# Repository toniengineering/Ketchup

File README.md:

So this is KETCHUP based on a ketchup bottle but with a little twist. So I like ketchup and with the pcb board I was inspired to use it in the project. With this I made the pcb base look like a ketchup bottle. The LEDs on it form a cap at the top then will blink in a little wave loop under it. It starts at ketchup, then loop, then the word finish where the last LED is.

BOM:

|Name   |Purpose|Quantity|Total Cost (USD)|Link                                  |Distributor|
|-------|-------|--------|----------------|--------------------------------------|-----------|
|Ketchup|my pcb |5       |2.00            |https://cart.jlcpcb.com/shopcart/cart/|JLCPCB     |

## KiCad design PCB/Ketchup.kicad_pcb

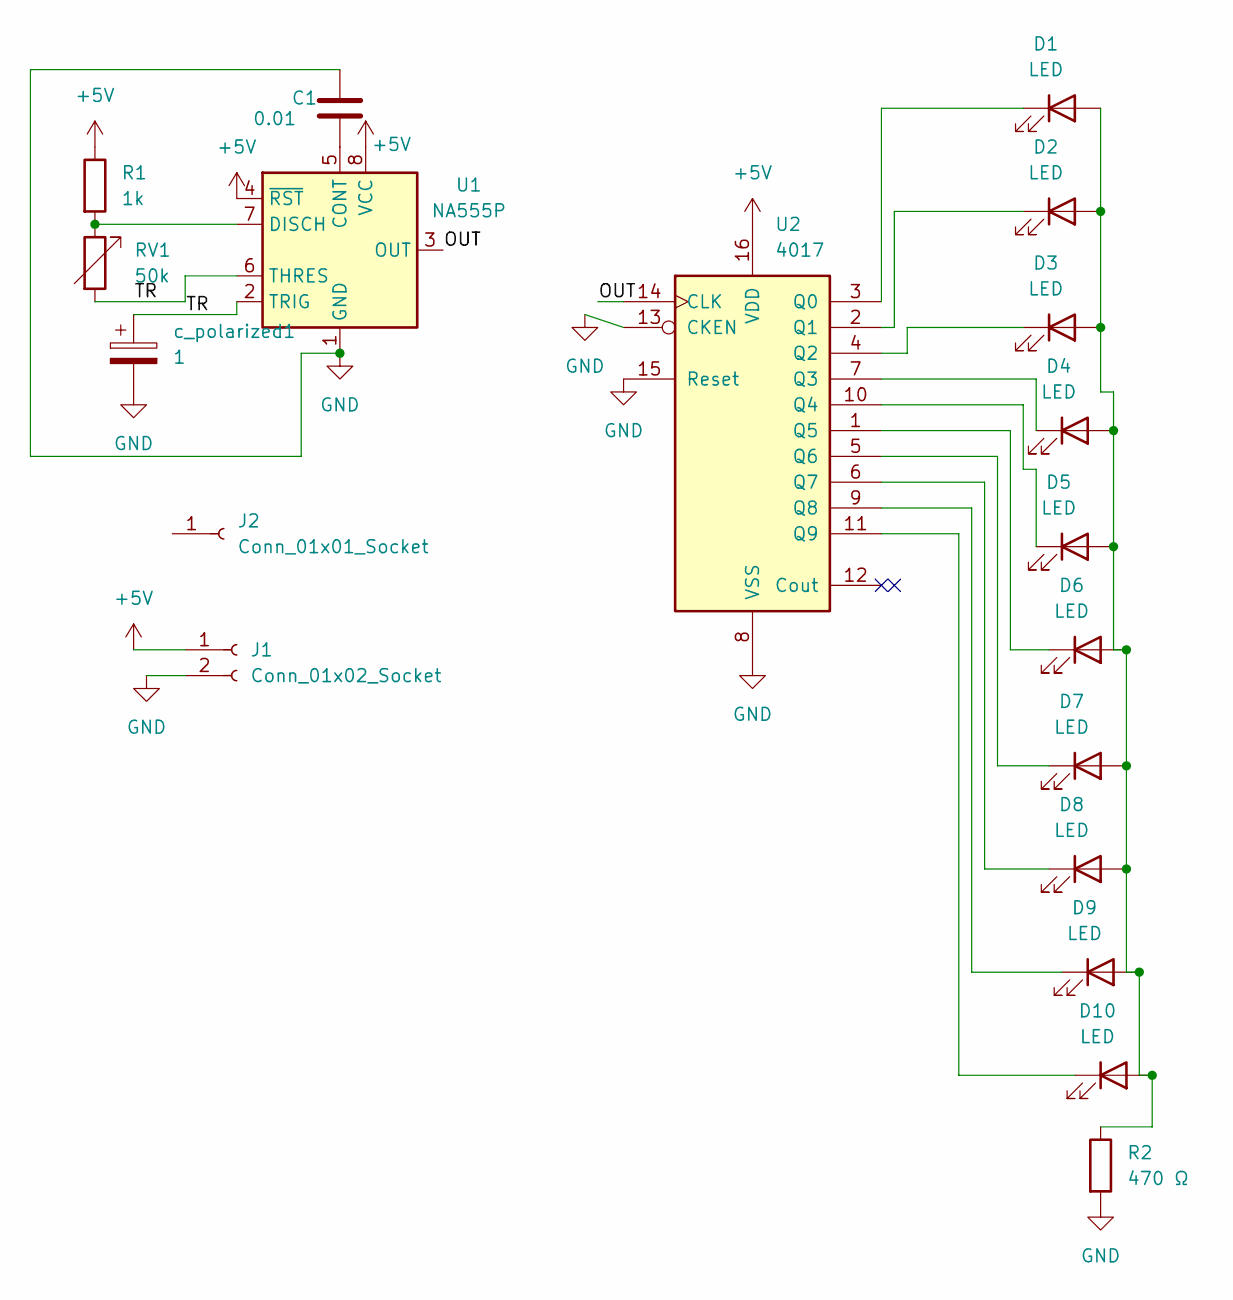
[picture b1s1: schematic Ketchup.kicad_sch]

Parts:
C1: 0.01; CP_Radial_D5.0mm_P2.00mm
D1, D2, D3, D4, D5, D6, D7, D8, D9, D10: LED; LED_D3.0mm
J1: Conn_01x02_Socket; PinHeader_1x02_P2.54mm_Vertical
J2: Conn_01x01_Socket; PinHeader_1x02_P2.54mm_Vertical
R1: 1k; R_Axial_DIN0207_L6.3mm_D2.5mm_P7.62mm_Horizontal
R2: 470 Ω; R_Axial_DIN0207_L6.3mm_D2.5mm_P7.62mm_Horizontal
RV1: 50k; Potentiometer_Vishay_T93YA_Vertical
U1: NA555P; DIP-8_W7.62mm
U2: 4017; N16
c_polarized1: 1; C_Disc_D7.5mm_W2.5mm_P5.00mm

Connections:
+5V: J1.1, R1.1, U1.4 (~RST), U1.8 (VCC), U2.16 (VDD)
/OUT: U1.3 (OUT), U2.14 (CLK)
/TR: RV1.2, U1.2 (TRIG), U1.6 (THRES), c_polarized1.1
GND: C1.1, J1.2, R2.2, U1.1 (GND), U2.8 (VSS), U2.13 (CKEN), U2.15 (Reset), c_polarized1.2
unnamed: D1.2 (A), D2.2 (A), D3.2 (A), D4.2 (A), D5.2 (A), D6.2 (A), D7.2 (A), D8.2 (A), D9.2 (A), D10.2 (A), R2.1
unnamed: D1.1 (K), U2.3 (Q0)
unnamed: D2.1 (K), U2.2 (Q1)
unnamed: D3.1 (K), U2.4 (Q2)
unnamed: D4.1 (K), U2.7 (Q3)
unnamed: D5.1 (K), U2.10 (Q4)
unnamed: D6.1 (K), U2.1 (Q5)
unnamed: D7.1 (K), U2.5 (Q6)
unnamed: D8.1 (K), U2.6 (Q7)
unnamed: D9.1 (K), U2.9 (Q8)
unnamed: D10.1 (K), U2.11 (Q9)
unnamed: C1.2, U1.5 (CONT)
unnamed: R1.2, RV1.1, U1.7 (DISCH)

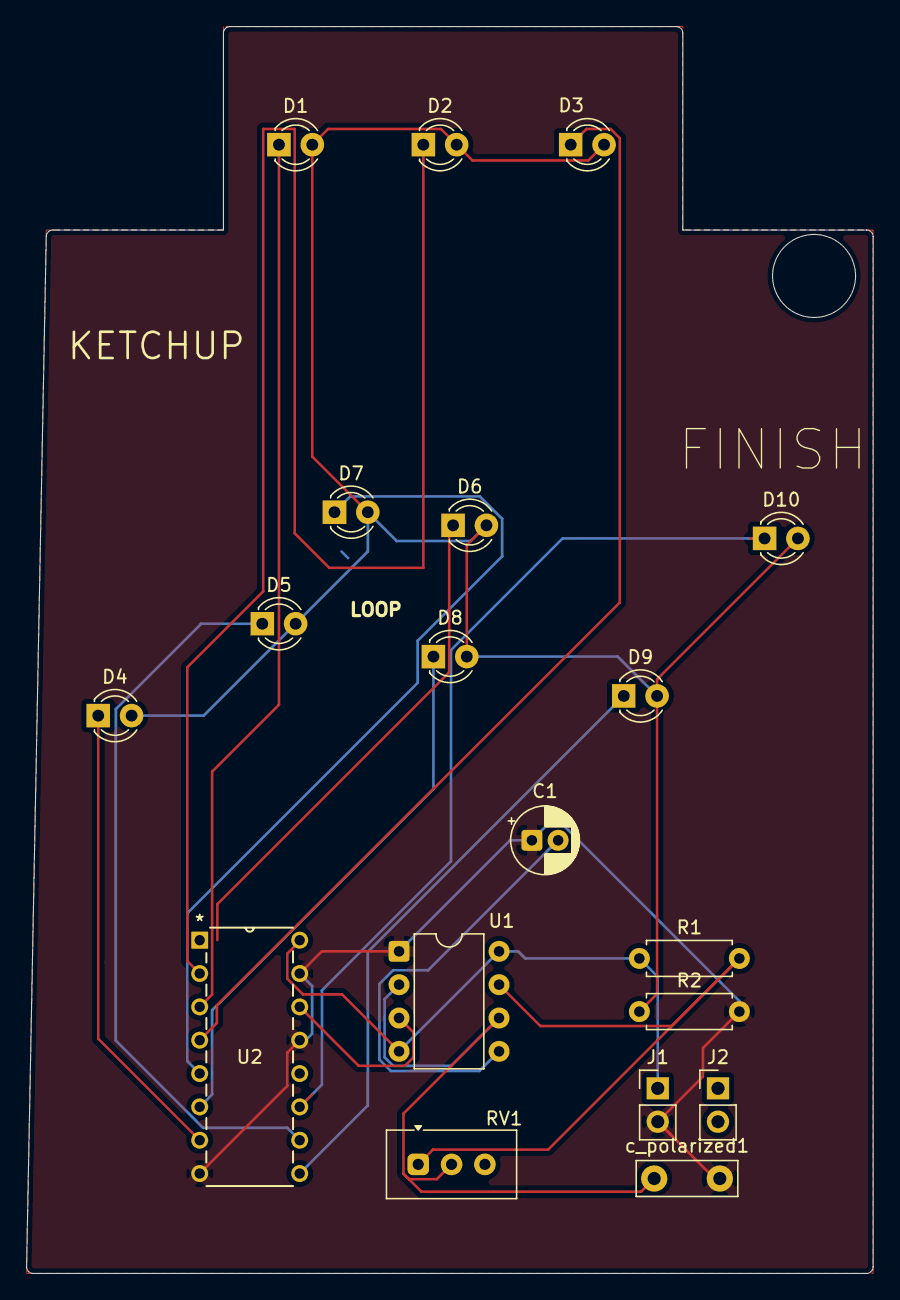
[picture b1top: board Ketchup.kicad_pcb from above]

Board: 2 copper layers, 64.5 x 95.0 mm, 19 parts (0 on the bottom side), 17 nets.

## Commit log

2026-06-13 Create s
2026-06-13 Create d
2026-06-13 Create BOM
2026-06-13 Create B
2026-06-13 Add BOM section to README
    Added BOM section with details for components.
